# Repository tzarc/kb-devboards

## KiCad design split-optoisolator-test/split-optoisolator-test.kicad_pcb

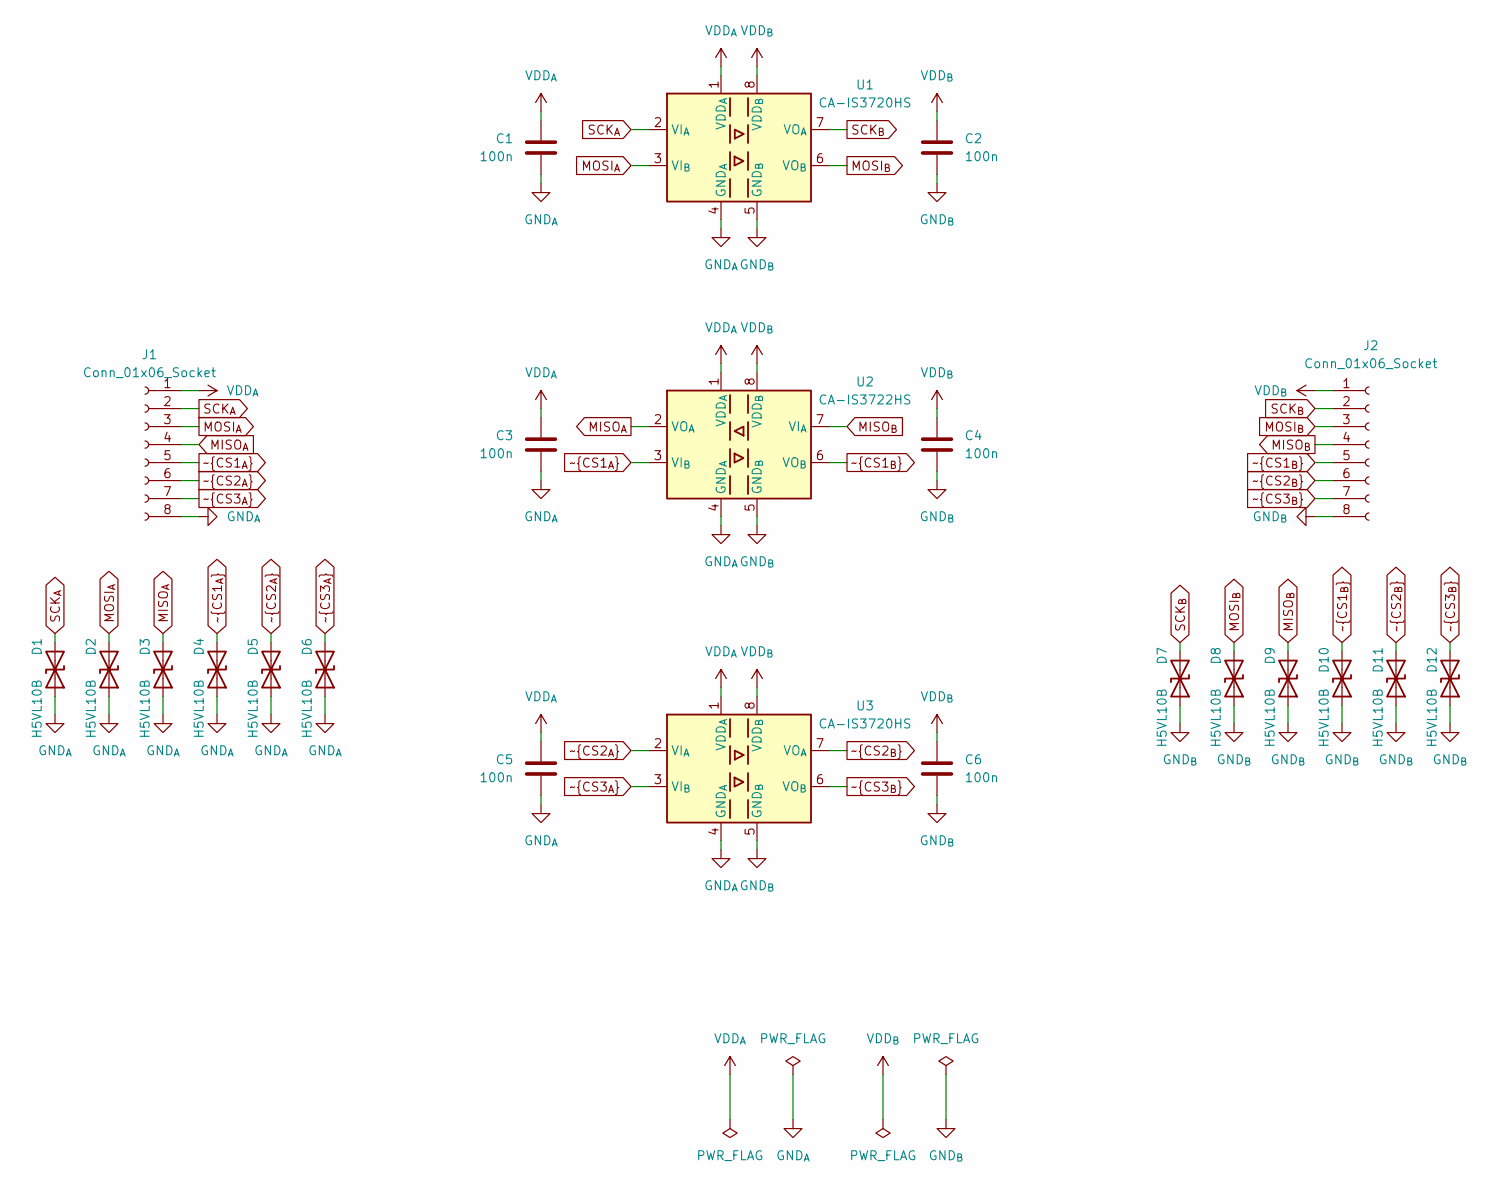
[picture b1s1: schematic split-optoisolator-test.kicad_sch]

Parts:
C1, C2, C3, C4, C5, C6: 100n; C_0402_1005Metric; LCSC C1525
D1, D2, D3, D4, D5, D6, D7, D8, D9, D10, D11, D12: H5VL10B; D_SOD-882D; LCSC C7420372
J1, J2: Conn_01x06_Socket; PinHeader_1x08_P2.54mm_Vertical
U1, U3: CA-IS3720HS; SOIC-8_3.9x4.9mm_P1.27mm; LCSC C428882
U2: CA-IS3722HS; SOIC-8_3.9x4.9mm_P1.27mm; LCSC C428879

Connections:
GND_{A}: C1.2, C3.2, C5.2, D1.1 (A1), D2.1 (A1), D3.1 (A1), D4.1 (A1), D5.1 (A1), D6.1 (A1), J1.8, U1.4 (GND_{A}), U2.4 (GND_{A}), U3.4 (GND_{A})
GND_{B}: C2.2, C4.2, C6.2, D7.1 (A1), D8.1 (A1), D9.1 (A1), D10.1 (A1), D11.1 (A1), D12.1 (A1), J2.8, U1.5 (GND_{B}), U2.5 (GND_{B}), U3.5 (GND_{B})
MISO_{A}: D3.2 (A2), J1.4, U2.2 (VO_{A})
MISO_{B}: D9.2 (A2), J2.4, U2.7 (VI_{A})
MOSI_{A}: D2.2 (A2), J1.3, U1.3 (VI_{B})
MOSI_{B}: D8.2 (A2), J2.3, U1.6 (VO_{B})
SCK_{A}: D1.2 (A2), J1.2, U1.2 (VI_{A})
SCK_{B}: D7.2 (A2), J2.2, U1.7 (VO_{A})
VDD_{A}: C1.1, C3.1, C5.1, J1.1, U1.1 (VDD_{A}), U2.1 (VDD_{A}), U3.1 (VDD_{A})
VDD_{B}: C2.1, C4.1, C6.1, J2.1, U1.8 (VDD_{B}), U2.8 (VDD_{B}), U3.8 (VDD_{B})
~CS1_{A}: D4.2 (A2), J1.5, U2.3 (VI_{B})
~CS1_{B}: D10.2 (A2), J2.5, U2.6 (VO_{B})
~CS2_{A}: D5.2 (A2), J1.6, U3.2 (VI_{A})
~CS2_{B}: D11.2 (A2), J2.6, U3.7 (VO_{A})
~CS3_{A}: D6.2 (A2), J1.7, U3.3 (VI_{B})
~CS3_{B}: D12.2 (A2), J2.7, U3.6 (VO_{B})

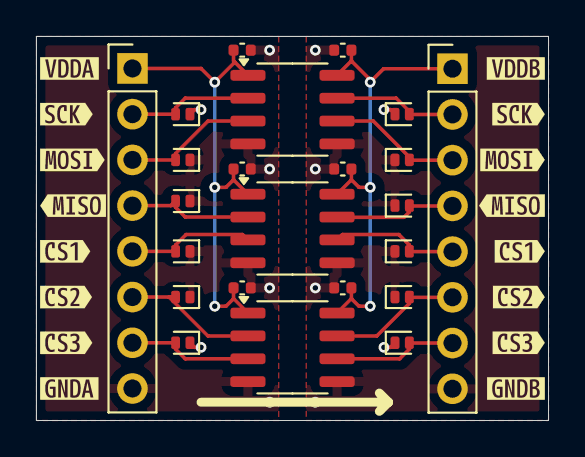
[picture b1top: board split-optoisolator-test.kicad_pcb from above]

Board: 2 copper layers, 28.4 x 21.3 mm, 39 parts (0 on the bottom side), 16 nets.

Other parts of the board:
kibuzzard-673DCC8F, kibuzzard-673DCC8F#2: G***; kibuzzard-673DCC8F
kibuzzard-673DCC9C, kibuzzard-673DCC9C#2: G***; kibuzzard-673DCC9C
kibuzzard-673DCC85, kibuzzard-673DCC85#2: G***; kibuzzard-673DCC85
kibuzzard-673DCCC0, kibuzzard-673DCCC0#2: G***; kibuzzard-673DCCC0
kibuzzard-673DCCC9, kibuzzard-673DCCC9#2: G***; kibuzzard-673DCCC9
kibuzzard-673DCCD2, kibuzzard-673DCCD2#2: G***; kibuzzard-673DCCD2
kibuzzard-673DCCE0: G***; kibuzzard-673DCCE0
kibuzzard-673DCCEB: G***; kibuzzard-673DCCEB
kibuzzard-673DCCFF: G***; kibuzzard-673DCCFF
kibuzzard-673DCD04: G***; kibuzzard-673DCD04

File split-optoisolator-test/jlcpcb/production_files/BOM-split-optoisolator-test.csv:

Comment,Designator,Footprint,LCSC
100n,"C1,C2,C3,C4,C5,C6",C_0402_1005Metric,C1525
CA-IS3722HS,U2,SOIC-8_3.9x4.9mm_P1.27mm,C428879
CA-IS3720HS,"U1,U3",SOIC-8_3.9x4.9mm_P1.27mm,C428882
H5VL10B,"D1,D10,D11,D12,D2,D3,D4,D5,D6,D7,D8,D9",D_SOD-882D,C7420372

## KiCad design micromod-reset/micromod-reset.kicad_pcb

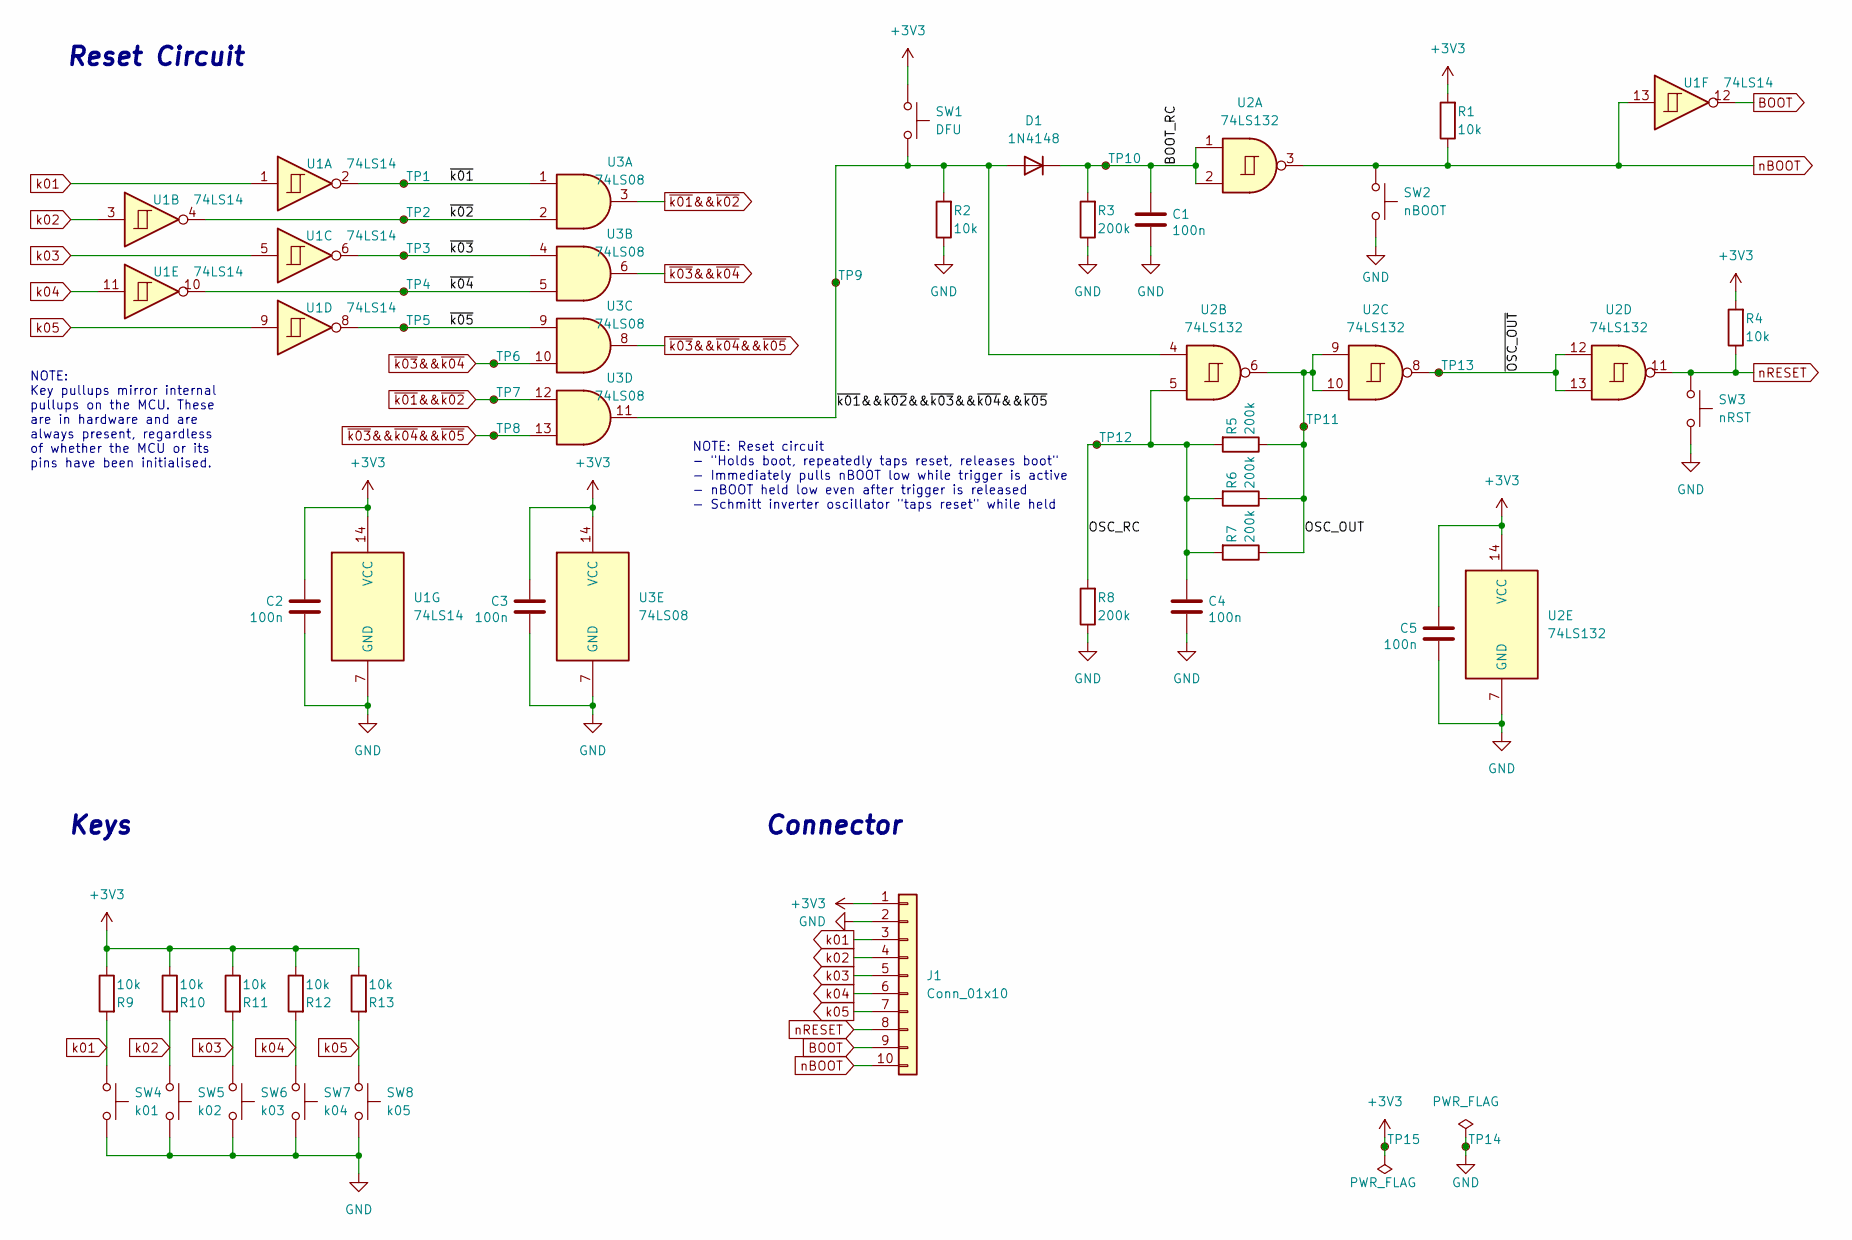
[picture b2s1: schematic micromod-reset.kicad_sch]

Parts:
C1, C2, C3, C4, C5: 100n; C_0402_1005Metric; LCSC C1525
D1: 1N4148; D_SOD-123F; LCSC C81598
J1: Conn_01x10; PinHeader_1x10_P2.54mm_Vertical
R1, R2, R4, R9, R10, R11, R12, R13: 10k; R_0402_1005Metric; LCSC C25764
R3, R5, R6, R7, R8: 200k; R_0402_1005Metric; LCSC C25764
SW1: DFU; SW_PUSH_6mm
SW2: nBOOT; SW_PUSH_6mm
SW3: nRST; SW_PUSH_6mm
SW4: k01; SW_PUSH_6mm
SW5: k02; SW_PUSH_6mm
SW6: k03; SW_PUSH_6mm
SW7: k04; SW_PUSH_6mm
SW8: k05; SW_PUSH_6mm
TP1, TP2, TP3, TP4, TP5, TP6, TP7, TP8, TP9, TP10, TP11, TP12, TP13, TP14, TP15: TestPoint_Small; TestPoint_Loop_D3.50mm_Drill1.4mm_Beaded
U1: 74LS14; SOIC-14_3.9x8.7mm_P1.27mm; LCSC C5605
U2: 74LS132; SOIC-14_3.9x8.7mm_P1.27mm; LCSC C7332
U3: 74LS08; SOIC-14_3.9x8.7mm_P1.27mm; LCSC C5593

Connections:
+3V3: C2.1, C3.1, C5.1, J1.1, R1.2, R4.2, R9.1, R10.1, R11.1, R12.1, R13.1, SW1.1, TP15.1, U1.14 (VCC), U2.14 (VCC), U3.14 (VCC)
/BOOT_RC: C1.1, D1.1 (K), R3.2, TP10.1, U2.1, U2.2
/OSC_OUT: R5.1, R6.1, R7.1, TP11.1, U2.6, U2.9, U2.10
/OSC_RC: C4.1, R5.2, R6.2, R7.2, R8.2, TP12.1, U2.5
/~OSC_OUT: TP13.1, U2.8, U2.12, U2.13
/~k01: TP1.1, U1.2, U3.1
/~k01&&~k02&&~k03&&~k04&&~k05: D1.2 (A), R2.2, SW1.2, TP9.1, U2.4, U3.11
/~k02: TP2.1, U1.4, U3.2
/~k03: TP3.1, U1.6, U3.4
/~k04: TP4.1, U1.10, U3.5
/~k05: TP5.1, U1.8, U3.9
BOOT: J1.9, U1.12
GND: C1.2, C2.2, C3.2, C4.2, C5.2, J1.2, R2.1, R3.1, R8.1, SW2.2, SW3.2, SW4.2, SW5.2, SW6.2, SW7.2, SW8.2, TP14.1, U1.7 (GND), U2.7 (GND), U3.7 (GND)
k01: J1.3, R9.2, SW4.1, U1.1
k02: J1.4, R10.2, SW5.1, U1.3
k03: J1.5, R11.2, SW6.1, U1.5
k04: J1.6, R12.2, SW7.1, U1.11
k05: J1.7, R13.2, SW8.1, U1.9
nBOOT: J1.10, R1.1, SW2.1, U1.13, U2.3
nRESET: J1.8, R4.1, SW3.1, U2.11
~k01&&~k02: TP7.1, U3.3, U3.12
~k03&&~k04: TP6.1, U3.6, U3.10
~k03&&~k04&&~k05: TP8.1, U3.8, U3.13

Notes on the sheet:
NOTE: Reset circuit - "Holds boot, repeatedly taps reset, releases boot" - Immediately pulls nBOOT low while trigger is active - nBOOT held low even after trigger is released - Schmitt inverter oscillator "taps reset" while held
Reset Circuit
Keys
NOTE: Key pullups mirror internal pullups on the MCU. These are in hardware and are always present, regardless of whether the MCU or its pins have been initialised.
Connector

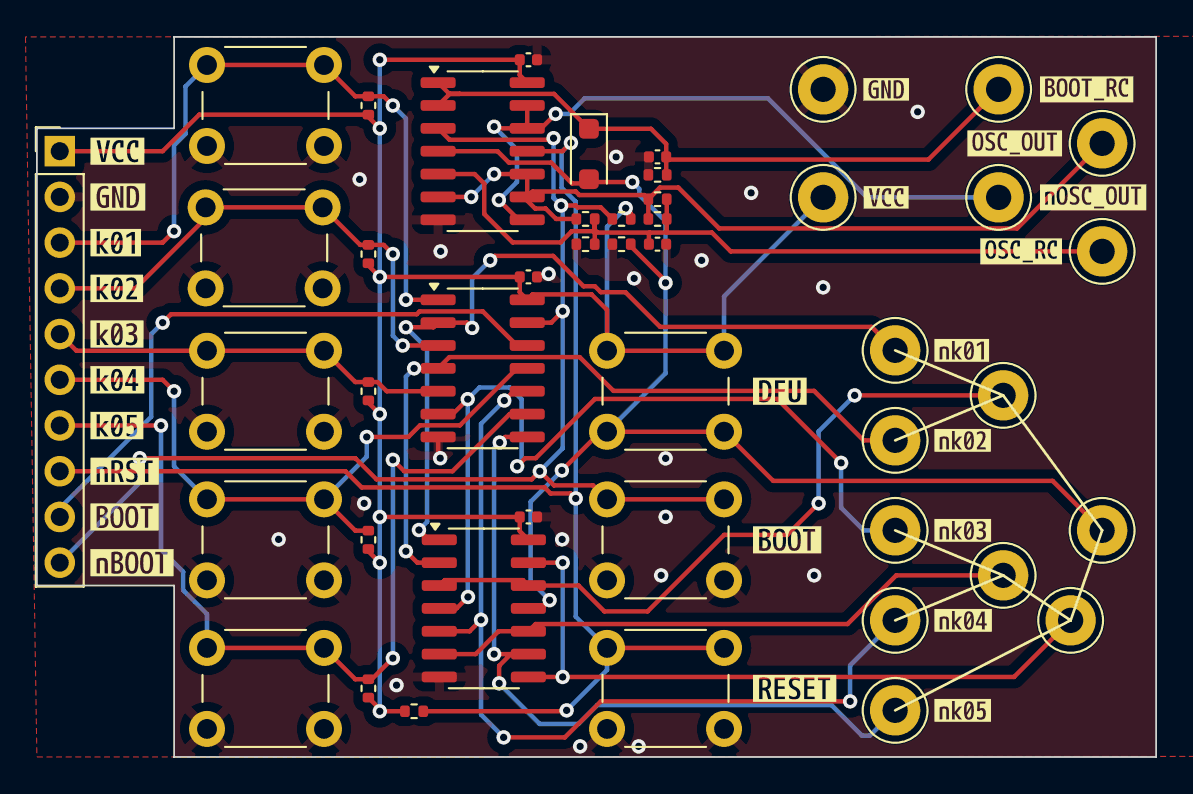
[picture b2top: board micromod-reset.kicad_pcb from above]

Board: 2 copper layers, 62.2 x 40.0 mm, 70 parts (0 on the bottom side), 23 nets.

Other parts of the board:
kibuzzard-66AE2A2C: G***; kibuzzard-66AE2A2C
kibuzzard-66AE2A3F: G***; kibuzzard-66AE2A3F
kibuzzard-66AE2A4E: G***; kibuzzard-66AE2A4E
kibuzzard-66AE2A6F: G***; kibuzzard-66AE2A6F
kibuzzard-66AE2A7C: G***; kibuzzard-66AE2A7C
kibuzzard-66AE2A35: G***; kibuzzard-66AE2A35
kibuzzard-66AE2A46: G***; kibuzzard-66AE2A46
kibuzzard-66AE2A58: G***; kibuzzard-66AE2A58
kibuzzard-66AE2A61: G***; kibuzzard-66AE2A61
kibuzzard-66AE2A86: G***; kibuzzard-66AE2A86
kibuzzard-66AE2AD3: G***; kibuzzard-66AE2AD3
kibuzzard-66AE2AE7: G***; kibuzzard-66AE2AE7
kibuzzard-66AE2B01: G***; kibuzzard-66AE2B01
kibuzzard-66C2A7CC: G***; kibuzzard-66C2A7CC
kibuzzard-66C2A8B2: G***; kibuzzard-66C2A8B2
kibuzzard-66C2A9A5: G***; kibuzzard-66C2A9A5
kibuzzard-66C2A9AD: G***; kibuzzard-66C2A9AD
kibuzzard-66C2A80C: G***; kibuzzard-66C2A80C
kibuzzard-66C2A89E: G***; kibuzzard-66C2A89E
kibuzzard-66C2A98F: G***; kibuzzard-66C2A98F
kibuzzard-66C2A99F: G***; kibuzzard-66C2A99F
kibuzzard-66C2A818: G***; kibuzzard-66C2A818
kibuzzard-66C2A826: G***; kibuzzard-66C2A826
kibuzzard-66C2A998: G***; kibuzzard-66C2A998

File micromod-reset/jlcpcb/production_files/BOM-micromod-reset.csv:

Comment,Designator,Footprint,LCSC
100n,"C1,C2,C3,C4,C5",C_0402_1005Metric,C1525
200k,"R1,R10,R11,R12,R13,R2,R3,R4,R5,R6,R7,R8,R9",R_0402_1005Metric,C25764
74LS08,U3,SOIC-14_3.9x8.7mm_P1.27mm,C5593
74LS14,U1,SOIC-14_3.9x8.7mm_P1.27mm,C5605
74LS132,U2,SOIC-14_3.9x8.7mm_P1.27mm,C7332
1N4148,D1,D_SOD-123F,C81598
k05,SW8,SW_PUSH_6mm,
k04,SW7,SW_PUSH_6mm,
k03,SW6,SW_PUSH_6mm,
k02,SW5,SW_PUSH_6mm,
k01,SW4,SW_PUSH_6mm,
nRST,SW3,SW_PUSH_6mm,
nBOOT,SW2,SW_PUSH_6mm,
DFU,SW1,SW_PUSH_6mm,
Conn_01x10,J1,PinHeader_1x10_P2.54mm_Vertical,
TestPoint_Small,TP14,TestPoint_Loop_D3.50mm_Drill1.4mm_Beaded,
TestPoint_Small,TP5,TestPoint_Loop_D3.50mm_Drill1.4mm_Beaded,
TestPoint_Small,TP8,TestPoint_Loop_D3.50mm_Drill1.4mm_Beaded,
TestPoint_Small,TP2,TestPoint_Loop_D3.50mm_Drill1.4mm_Beaded,
TestPoint_Small,TP12,TestPoint_Loop_D3.50mm_Drill1.4mm_Beaded,
TestPoint_Small,TP3,TestPoint_Loop_D3.50mm_Drill1.4mm_Beaded,
TestPoint_Small,TP10,TestPoint_Loop_D3.50mm_Drill1.4mm_Beaded,
TestPoint_Small,TP6,TestPoint_Loop_D3.50mm_Drill1.4mm_Beaded,
TestPoint_Small,TP1,TestPoint_Loop_D3.50mm_Drill1.4mm_Beaded,
TestPoint_Small,TP11,TestPoint_Loop_D3.50mm_Drill1.4mm_Beaded,
TestPoint_Small,TP9,TestPoint_Loop_D3.50mm_Drill1.4mm_Beaded,
TestPoint_Small,TP13,TestPoint_Loop_D3.50mm_Drill1.4mm_Beaded,
TestPoint_Small,TP7,TestPoint_Loop_D3.50mm_Drill1.4mm_Beaded,
TestPoint_Small,TP15,TestPoint_Loop_D3.50mm_Drill1.4mm_Beaded,
TestPoint_Small,TP4,TestPoint_Loop_D3.50mm_Drill1.4mm_Beaded,

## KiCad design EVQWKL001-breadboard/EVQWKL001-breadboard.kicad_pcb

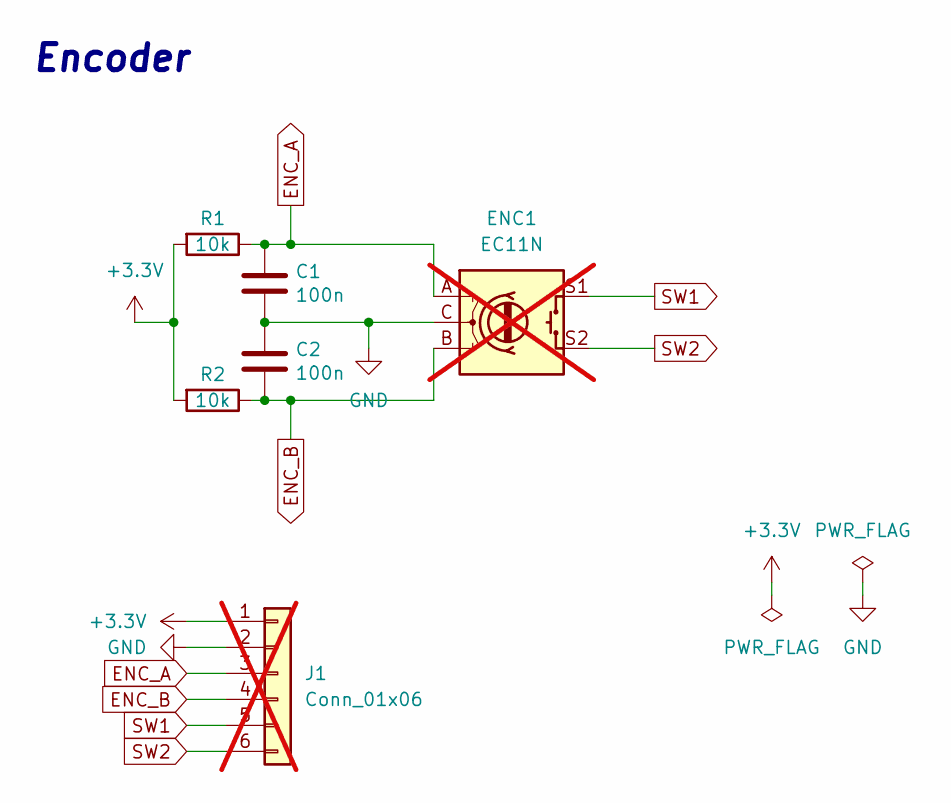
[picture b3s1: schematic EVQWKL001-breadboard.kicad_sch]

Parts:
C1, C2: 100n; C_0805_2012Metric
ENC1: EC11N; Encoder_EVQWKL001; not fitted
J1: Conn_01x06; PinHeader_1x06_P2.54mm_Vertical; not fitted
R1, R2: 10k; R_0805_2012Metric

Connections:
+3.3V: J1.1, R1.2, R2.2
ENC_A: C1.1, ENC1.A, J1.3, R1.1
ENC_B: C2.2, ENC1.B, J1.4, R2.1
GND: C1.2, C2.1, ENC1.C, J1.2
SW1: ENC1.S1, J1.5
SW2: ENC1.S2, J1.6

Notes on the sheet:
Encoder

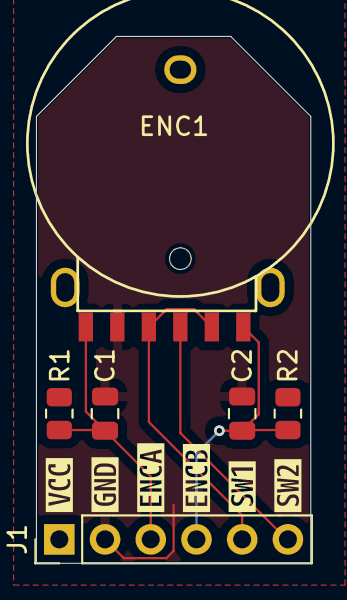
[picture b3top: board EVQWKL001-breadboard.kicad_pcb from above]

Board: 2 copper layers, 15.2 x 29.3 mm, 12 parts (0 on the bottom side), 6 nets.

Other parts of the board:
kibuzzard-66AE0B80: G***; kibuzzard-66AE0B80
kibuzzard-66AE0B89: G***; kibuzzard-66AE0B89
kibuzzard-66AE0B98: G***; kibuzzard-66AE0B98
kibuzzard-66AE0BA5: G***; kibuzzard-66AE0BA5
kibuzzard-66AE0BAD: G***; kibuzzard-66AE0BAD
kibuzzard-66AE0BB5: G***; kibuzzard-66AE0BB5

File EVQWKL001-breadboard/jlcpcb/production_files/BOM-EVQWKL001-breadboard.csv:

Comment,Designator,Footprint,LCSC
100n,C1,C_0805_2012Metric,
100n,C2,C_0805_2012Metric,
10k,R1,R_0805_2012Metric,
EC11N,,Encoder_EVQWKL001,
Conn_01x06,,PinHeader_1x06_P2.54mm_Vertical,
10k,R2,R_0805_2012Metric,

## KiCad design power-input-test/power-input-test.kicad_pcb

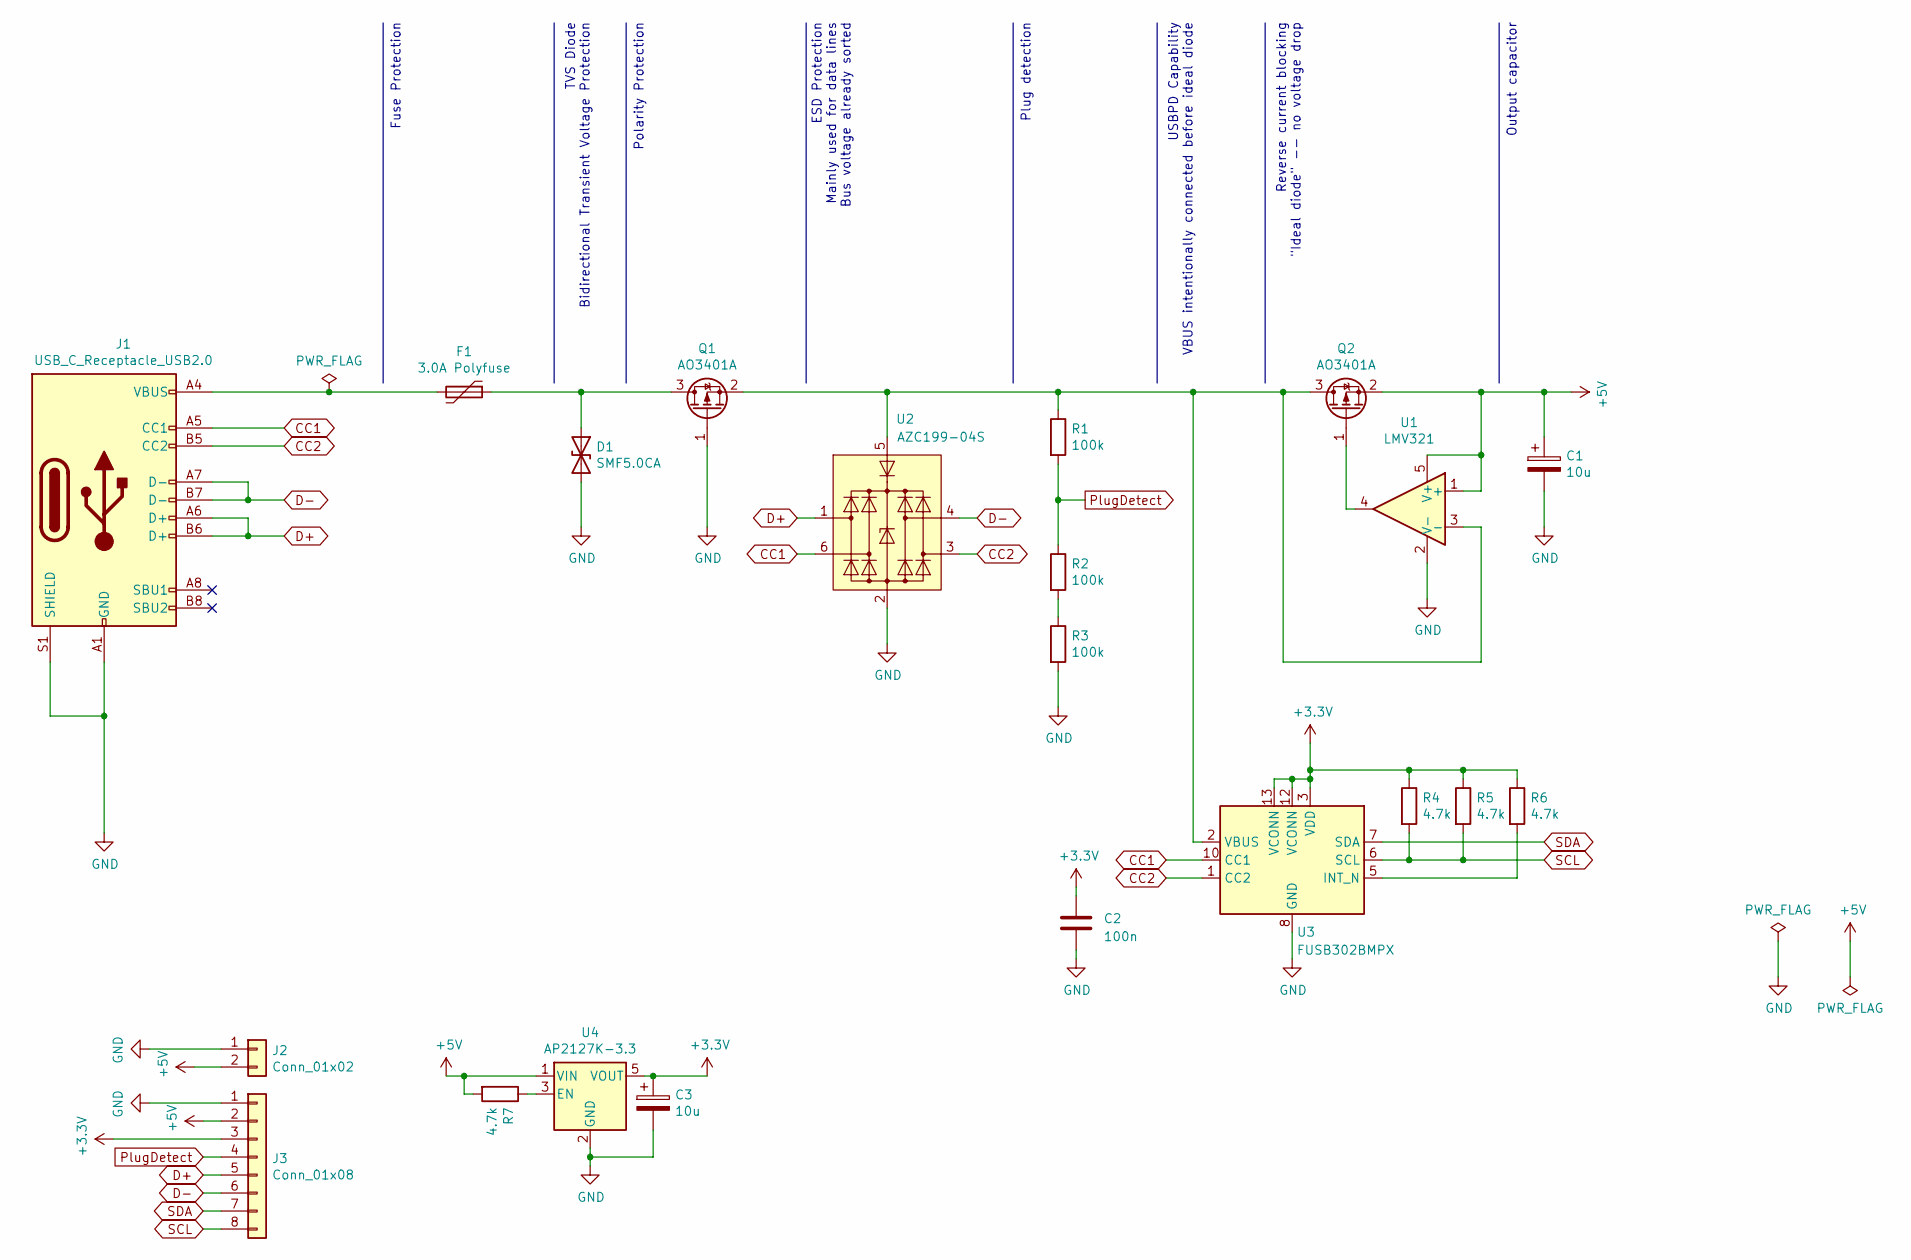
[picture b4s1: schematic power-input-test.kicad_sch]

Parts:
C1, C3: 10u; CP_EIA-3216-12_Kemet-S
C2: 100n; C_0402_1005Metric
D1: SMF5.0CA; D_SMB
F1: 3.0A Polyfuse; Fuse_1206_3216Metric
J1: USB_C_Receptacle_USB2.0; USB_C_Receptacle_HRO_TYPE-C-31-M-12
J2: Conn_01x02; PinHeader_1x02_P2.54mm_Vertical
J3: Conn_01x08; PinHeader_1x08_P2.54mm_Vertical
Q1, Q2: AO3401A; SOT-23
R1, R2, R3: 100k; R_0402_1005Metric
R4, R5, R6, R7: 4.7k; R_0402_1005Metric
U1: LMV321; SOT-23-5
U2: AZC199-04S; SOT-23-6
U3: FUSB302BMPX; WQFN-14-1EP_2.5x2.5mm_P0.5mm_EP1.45x1.45mm
U4: AP2127K-3.3; SOT-23-5

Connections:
+3.3V: C2.1, C3.1, J3.3, R4.1, R5.1, R6.1, U3.3 (VDD), U3.4 (VDD), U3.12 (VCONN), U3.13 (VCONN), U4.5 (VOUT)
+5V: C1.1, J2.2, J3.2, Q2.2 (S), R7.2, U1.1 (+), U1.5 (V+), U4.1 (VIN)
CC1: J1.A5 (CC1), U2.6 (I/O2), U3.10 (CC1), U3.11 (CC1)
CC2: J1.B5 (CC2), U2.3 (I/O4), U3.1 (CC2), U3.14 (CC2)
D+: J1.A6 (D+), J1.B6 (D+), J3.5, U2.1 (I/O1)
D-: J1.A7 (D-), J1.B7 (D-), J3.6, U2.4 (I/O3)
GND: C1.2, C2.2, C3.2, D1.2 (A2), J1.A1 (GND), J1.A12 (GND), J1.B1 (GND), J1.B12 (GND), J1.S1 (SHIELD), J2.1, J3.1, Q1.1 (G), R3.2, U1.2 (V-), U2.2 (GND), U3.8 (GND), U3.9 (GND), U3.15 (GND), U4.2 (GND)
unnamed: D1.1 (A1), F1.1, Q1.3 (D)
unnamed: F1.2, J1.A4 (VBUS), J1.A9 (VBUS), J1.B4 (VBUS), J1.B9 (VBUS)
unnamed: Q1.2 (S), Q2.3 (D), R1.1, U1.3 (-), U2.5 (VBUS), U3.2 (VBUS)
unnamed: Q2.1 (G), U1.4
unnamed: R2.2, R3.1
unnamed: R6.2, U3.5 (INT_N)
unnamed: R7.1, U4.3 (EN)
PlugDetect: J3.4, R1.2, R2.1
SCL: J3.8, R4.2, R5.2, U3.6 (SCL)
SDA: J3.7, U3.7 (SDA)

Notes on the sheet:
USBPD Capability VBUS intentionally connected before ideal diode
Polarity Protection
Plug detection
ESD Protection Mainly used for data lines Bus voltage already sorted
Output capacitor
Reverse current blocking "Ideal diode" -- no voltage drop
Fuse Protection
TVS Diode Bidirectional Transient Voltage Protection

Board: 2 copper layers, 21 parts (0 on the bottom side), 17 nets, no tracks yet.

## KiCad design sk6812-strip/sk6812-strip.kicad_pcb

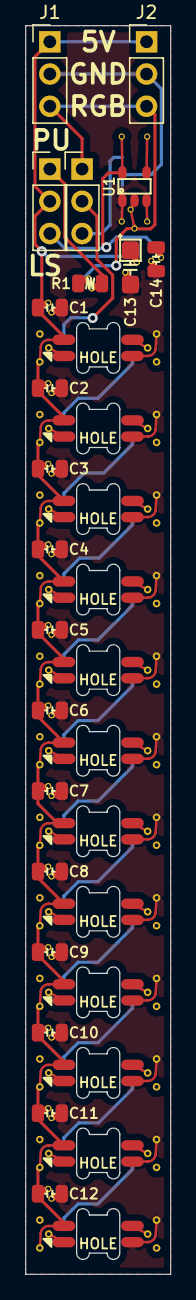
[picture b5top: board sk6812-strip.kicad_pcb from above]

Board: 2 copper layers, 11.4 x 98.4 mm, 32 parts (0 on the bottom side), 18 nets.

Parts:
C1, C2, C3, C4, C5, C6, C7, C8, C9, C10, C11, C12, C14: 100n; C-0805_2012Metric
C13: 10u; CP_3216
D1, D2, D3, D4, D5, D6, D7, D8, D9, D10, D11, D12: SK6812MINI; SK6812Mini-E
J1, J2, J3, J4: Conn_01x03; PinHeader_1x03_P2.54mm_Vertical
R1: 5k1; R-0805_2012Metric
U1: 74HCT1G125; SOT-23-5

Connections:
+5V: C1.1, C2.1, C3.1, C4.1, C5.1, C6.1, C7.1, C8.1, C9.1, C10.1, C11.1, C12.1, C13.1, D1.4, D2.4, D3.4, D4.4, D5.4, D6.4, D7.4, D8.4, D9.4, D10.4, D11.4, D12.4, J1.1, J2.1, J4.2
GND: C1.2, C2.2, C3.2, C4.2, C5.2, C6.2, C7.2, C8.2, C9.2, C10.2, C11.2, C12.2, C13.2, C14.2, D1.2, D2.2, D3.2, D4.2, D5.2, D6.2, D7.2, D8.2, D9.2, D10.2, D11.2, D12.2, J1.2, J2.2, U1.1, U1.3
unnamed: D1.1, D2.3
unnamed: D2.1, D3.3
unnamed: D3.1, D4.3
unnamed: D4.1, D5.3
unnamed: D5.1, D6.3
unnamed: D6.1, D7.3
unnamed: D7.1, D8.3
unnamed: D8.1, D9.3
unnamed: D10.1, D11.3
unnamed: D9.1, D10.3
unnamed: D11.1, D12.3
PULLUP_PWR: J4.1, R1.1
RGB_DI: D1.3, J3.2
RGB_IN: J1.3, J2.3, J3.1, R1.2, U1.2
SHIFTER_OUT: J3.3, U1.4
SHIFTER_PWR: C14.1, J4.3, U1.5

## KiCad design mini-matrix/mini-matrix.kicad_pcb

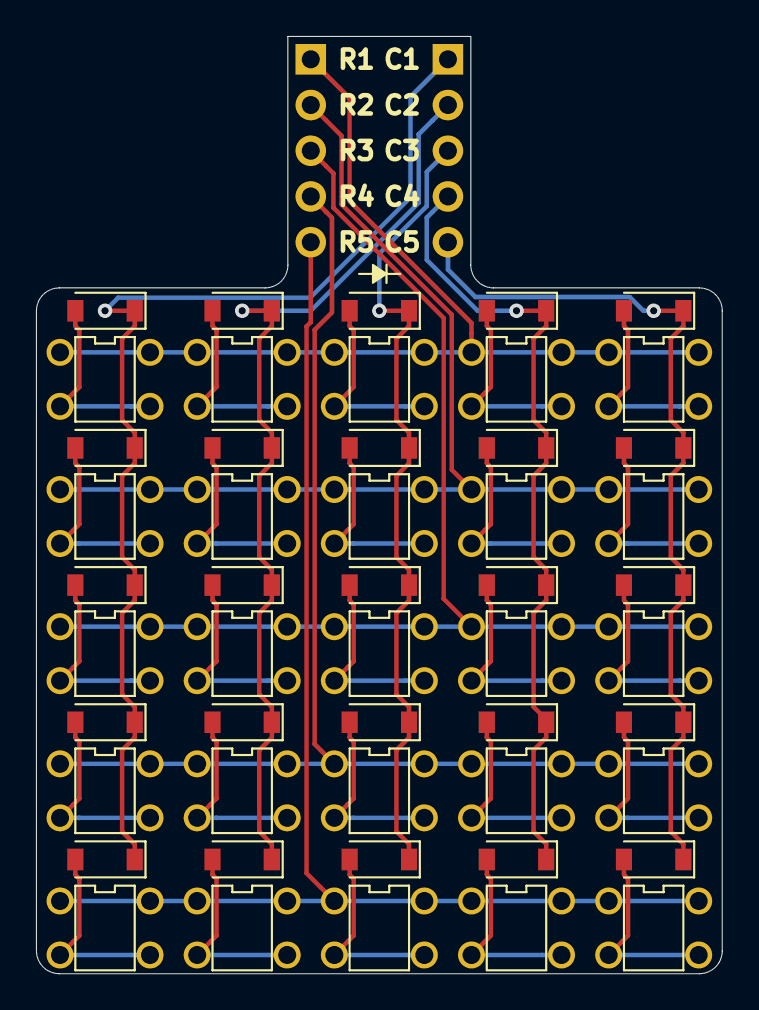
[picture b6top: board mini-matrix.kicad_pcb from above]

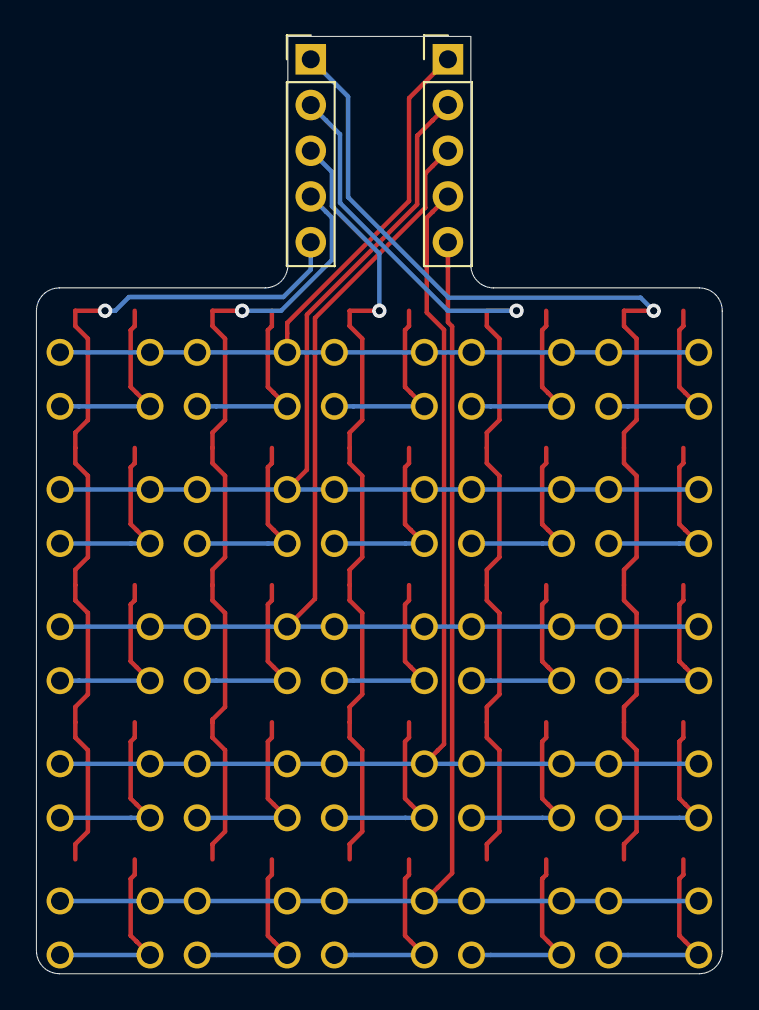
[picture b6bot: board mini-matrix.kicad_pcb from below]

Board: 2 copper layers, 38.1 x 52.1 mm, 52 parts (2 on the bottom side), 35 nets.

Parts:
D101, D102, D103, D104, D105, D106, D107, D108, D109, D110, D111, D112, D113, D114, D115, D116, D117, D118, D119, D120, D121, D122, D123, D124, D125: D_Small; D_SOD-123
J101, J102: Conn_01x05; PinHeader_1x05_P2.54mm_Vertical
SW101, SW102, SW103, SW104, SW105, SW106, SW107, SW108, SW109, SW110, SW111, SW112, SW113, SW114, SW115, SW116, SW117, SW118, SW119, SW120, SW121, SW122, SW123, SW124, SW125: SW_Push; PushButton_4.5mm

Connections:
unnamed: D101.2, SW101.2
unnamed: D102.2, SW102.2
unnamed: D103.2, SW103.2
unnamed: D104.2, SW104.2
unnamed: D105.2, SW105.2
unnamed: D106.2, SW106.2
unnamed: D107.2, SW107.2
unnamed: D108.2, SW108.2
unnamed: D109.2, SW109.2
unnamed: D110.2, SW110.2
unnamed: D111.2, SW111.2
unnamed: D112.2, SW112.2
unnamed: D113.2, SW113.2
unnamed: D114.2, SW114.2
unnamed: D115.2, SW115.2
unnamed: D116.2, SW116.2
unnamed: D117.2, SW117.2
unnamed: D118.2, SW118.2
unnamed: D119.2, SW119.2
unnamed: D120.2, SW120.2
unnamed: D121.2, SW121.2
unnamed: D122.2, SW122.2
unnamed: D123.2, SW123.2
unnamed: D124.2, SW124.2
unnamed: D125.2, SW125.2
col1: D101.1, D106.1, D111.1, D116.1, D121.1, J102.1
col2: D102.1, D107.1, D112.1, D117.1, D122.1, J102.2
col3: D103.1, D108.1, D113.1, D118.1, D123.1, J102.3
col4: D104.1, D109.1, D114.1, D119.1, D124.1, J102.4
col5: D105.1, D110.1, D115.1, D120.1, D125.1, J102.5
row1: J101.1, SW101.1, SW102.1, SW103.1, SW104.1, SW105.1
row2: J101.2, SW106.1, SW107.1, SW108.1, SW109.1, SW110.1
row3: J101.3, SW111.1, SW112.1, SW113.1, SW114.1, SW115.1
row4: J101.4, SW116.1, SW117.1, SW118.1, SW119.1, SW120.1
row5: J101.5, SW121.1, SW122.1, SW123.1, SW124.1, SW125.1

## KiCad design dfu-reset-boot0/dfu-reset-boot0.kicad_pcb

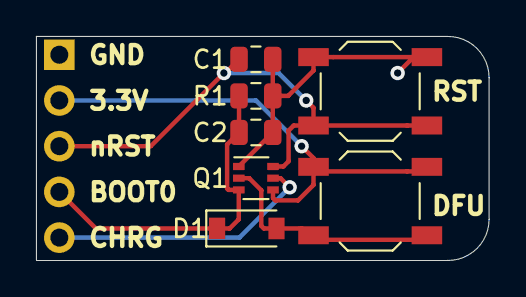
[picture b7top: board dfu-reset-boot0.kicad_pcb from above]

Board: 2 copper layers, 25.1 x 12.4 mm, 8 parts (1 on the bottom side), 6 nets.

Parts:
C1: 100n; C_0805_2012Metric
C2: 10u; C_0805_2012Metric
D1: 1N4148; D_SOD-123
DFU1: DFU; SW_SPST_TL3342
J1: Conn_01x05; PinHeader_1x05_P2.54mm_Vertical
Q1: MUN5333; SOT-363_SC-70-6
R1: 100k; R_0805_2012Metric
RESET1: RESET; SW_SPST_TL3342

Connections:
+3V3: DFU1.1, J1.2, Q1.4
BOOT0: C2.1, D1.1, J1.4, Q1.3, R1.1
BOOT0_CHRG: J1.5, Q1.5
GND: C1.2, C2.2, J1.1, Q1.1, R1.2, RESET1.1
NRST: C1.1, J1.3, Q1.6, RESET1.2
unnamed: D1.2, DFU1.2, Q1.2

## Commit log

2020-05-29 Initial commit for matrix, boot0/reset, power input.
2021-01-24 Rev2 power input
2021-01-31 Add SK6812 strip with selectable pullup or level shifter.
2021-11-30 Updated bom/pdf.
2024-08-18 Added defective micromod-reset circuit, untested EVQ circuit.
2024-08-19 micromod-reset, now with added test points and DRC success
2024-08-21 Updated JLC to match fixed circuit.
2024-08-21 Added micromod-reset PDF.
2024-11-21 Add SPI optoisolator test board.
